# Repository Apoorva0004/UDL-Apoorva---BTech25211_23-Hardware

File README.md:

# Astable Multivibrator PCB

This project contains the schematic and PCB design of an Astable Multivibrator created using KiCad.

## Features
- Dual transistor astable multivibrator
- Through-hole components
- Single layer PCB routing
- Gerber and drill files generated

## Design Details
- Track width used: 0.5 mm
- Silkscreen labels added
- Mounting holes included

## Files Included
- KiCad source files
- Gerber files
- Drill files
- BOM CSV
- Interactive BOM HTML
- Schematic PDF

## Resources Used
- KiCad documentation
- PCB routing tutorials
- BC547 datasheet

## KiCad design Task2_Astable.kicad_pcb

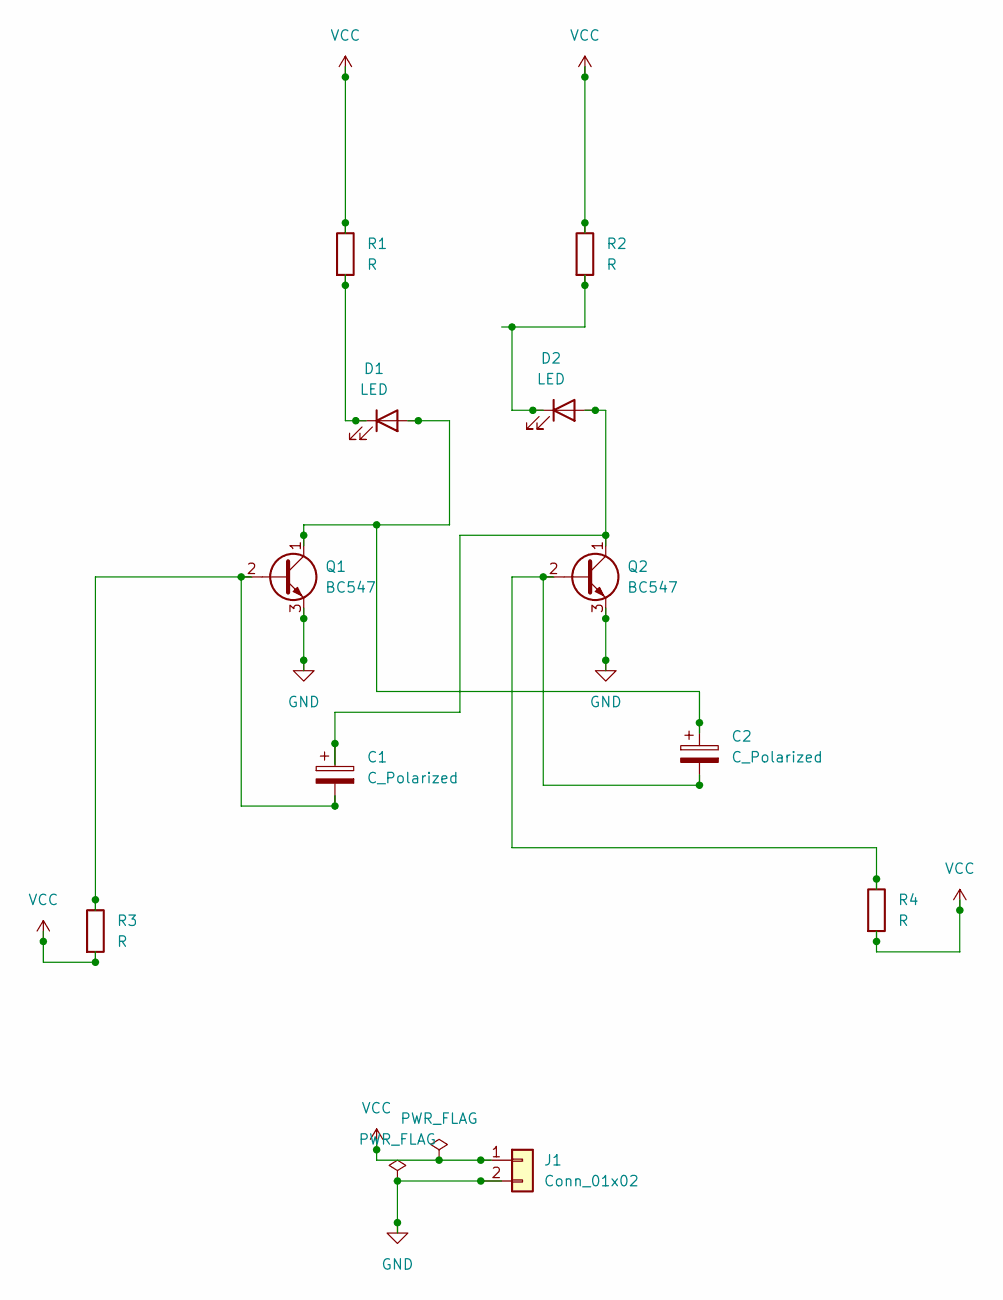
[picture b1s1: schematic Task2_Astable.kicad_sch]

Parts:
C1, C2: C_Polarized; CP_Radial_D5.0mm_P2.00mm
D1, D2: LED; LED_D5.0mm
J1: Conn_01x02; PinHeader_1x02_P2.54mm_Vertical
Q1, Q2: BC547; TO-92_Inline
R1, R2, R3, R4: R; R_Axial_DIN0207_L6.3mm_D2.5mm_P7.62mm_Horizontal

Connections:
GND: J1.2, Q1.3 (E), Q2.3 (E)
unnamed: C2.1, D1.2 (A), Q1.1 (C)
unnamed: D1.1 (K), R1.2
unnamed: C1.1, D2.2 (A), Q2.1 (C)
unnamed: D2.1 (K), R2.2
unnamed: C1.2, Q1.2 (B), R3.1
unnamed: C2.2, Q2.2 (B), R4.1
VCC: J1.1, R1.1, R2.1, R3.2, R4.2

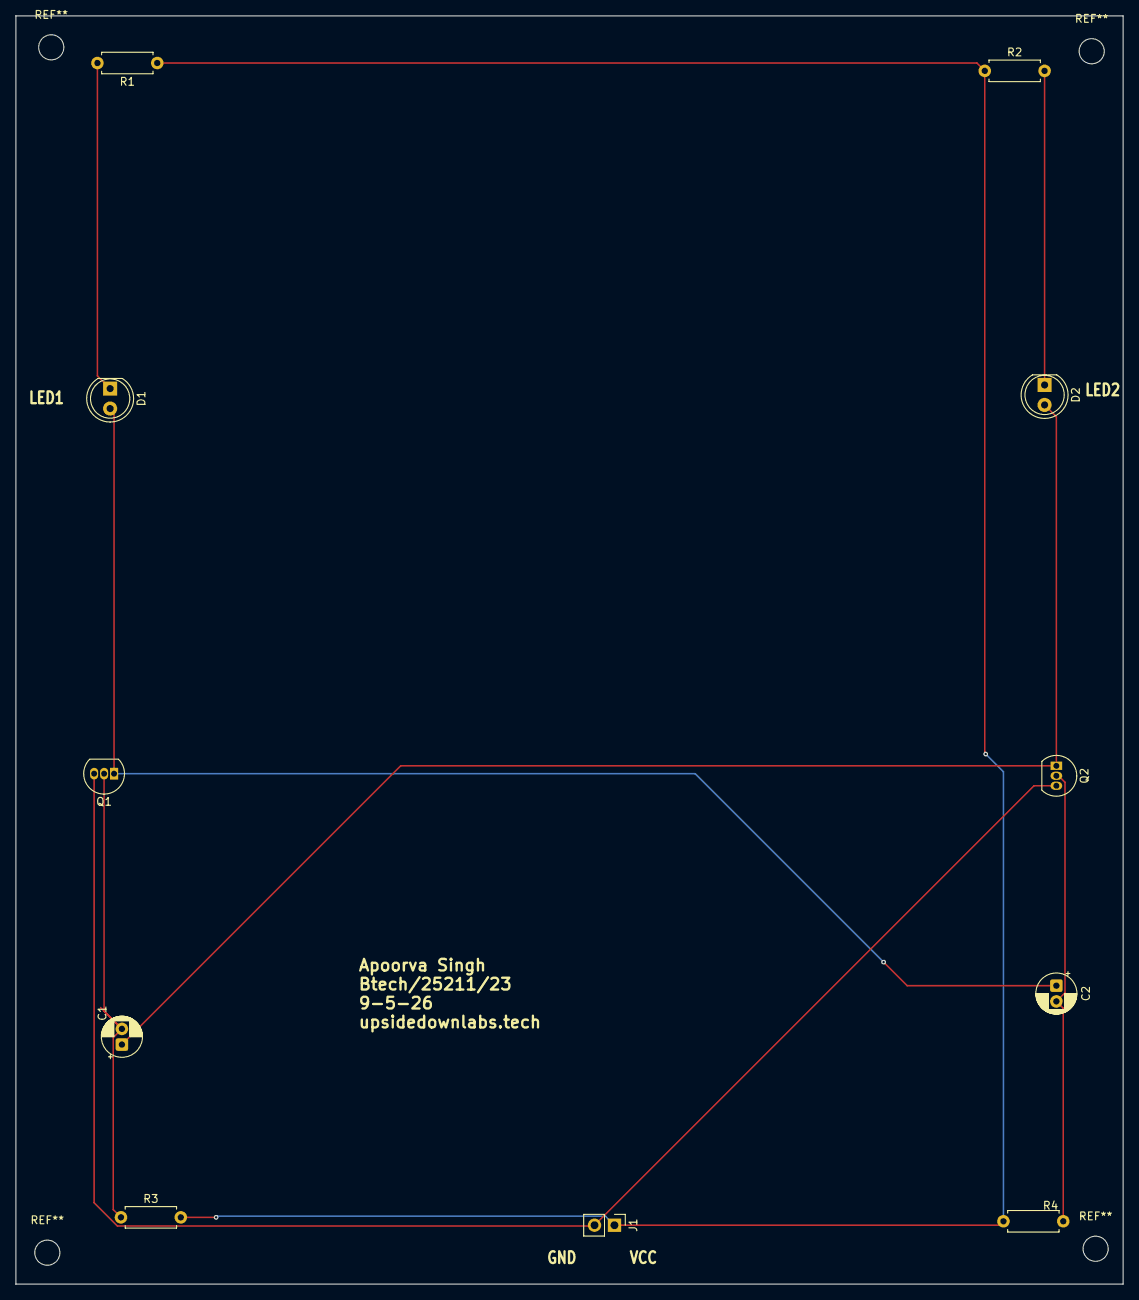
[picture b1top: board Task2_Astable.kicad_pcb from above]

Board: 2 copper layers, 141.0 x 161.5 mm, 11 parts (0 on the bottom side), 8 nets.

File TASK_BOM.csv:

"Reference","Qty","Value","DNP","Exclude from BOM","Exclude from Board","Footprint","Datasheet"
"C1,C2","2","C_Polarized","","","","Capacitor_THT:CP_Radial_D5.0mm_P2.00mm",""
"D1,D2","2","LED","","","","LED_THT:LED_D5.0mm",""
"J1","1","Conn_01x02","","","","Connector_PinHeader_2.54mm:PinHeader_1x02_P2.54mm_Vertical",""
"Q1,Q2","2","BC547","","","","Package_TO_SOT_THT:TO-92_Inline","https://www.onsemi.com/pub/Collateral/BC550-D.pdf"
"R1,R2,R3,R4","4","R","","","","Resistor_THT:R_Axial_DIN0207_L6.3mm_D2.5mm_P7.62mm_Horizontal",""

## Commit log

2026-05-11 Add files via upload
    schematic along with BOM
